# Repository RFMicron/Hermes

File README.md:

Hermes&trade;
=============

The Hermes&trade; IoT Development Platform enables exploration and development of Internet-of-Things
applications using passive wireless sensors built around the Magnus&reg;-S chip.

### Disclaimer

This material is provided "as is", without warranty of any kind, except as otherwise specified in
the individual files.

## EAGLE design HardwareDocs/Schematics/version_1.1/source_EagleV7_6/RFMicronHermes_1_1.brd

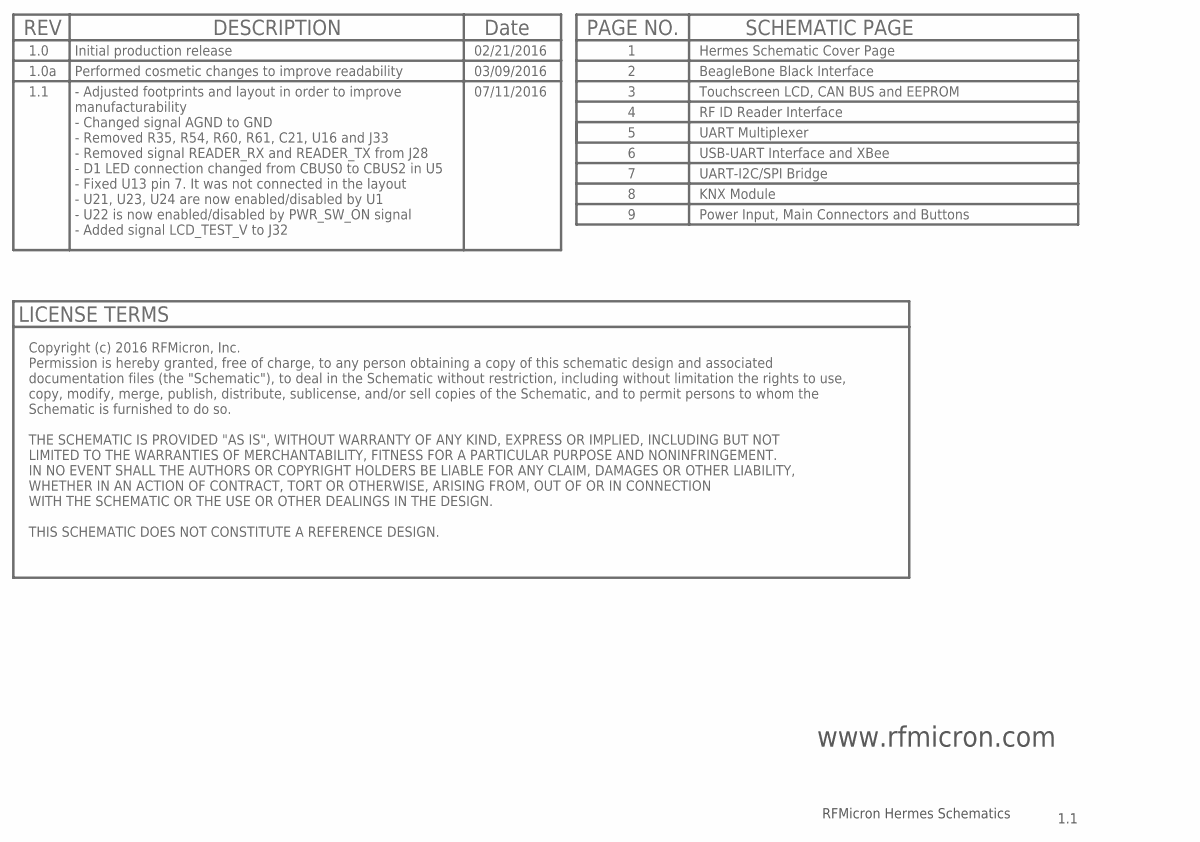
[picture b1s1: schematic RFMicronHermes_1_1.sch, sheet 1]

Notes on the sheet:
www.rfmicron.com
1.1
RFMicron Hermes Schematics
REV
DESCRIPTION
Date
02/21/2016
1.0
Initial production release
PAGE NO.
SCHEMATIC PAGE
Hermes Schematic Cover Page
LICENSE TERMS
Copyright (c) 2016 RFMicron, Inc. Permission is hereby granted, free of charge, to any person obtaining a copy of this schematic design and associated documentation files (the "Schematic"), to deal in the Schematic without restriction, including without limitation the rights to use, copy, modify, m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
BeagleBone Black Interface
Touchscreen LCD, CAN BUS and EEPROM
RF ID Reader Interface
UART Multiplexer
UART-I2C/SPI Bridge
USB-UART Interface and XBee
KNX Module
1.0a
03/09/2016
Performed cosmetic changes to improve readability
Power Input, Main Connectors and Buttons
07/11/2016
- Adjusted footprints and layout in order to improve manufacturability - Changed signal AGND to GND - Removed R35, R54, R60, R61, C21, U16 and J33 - Removed signal READER_RX and READER_TX from J28 - D1 LED connection changed from CBUS0 to CBUS2 in U5 - Fixed U13 pin 7. It was not connected in the l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

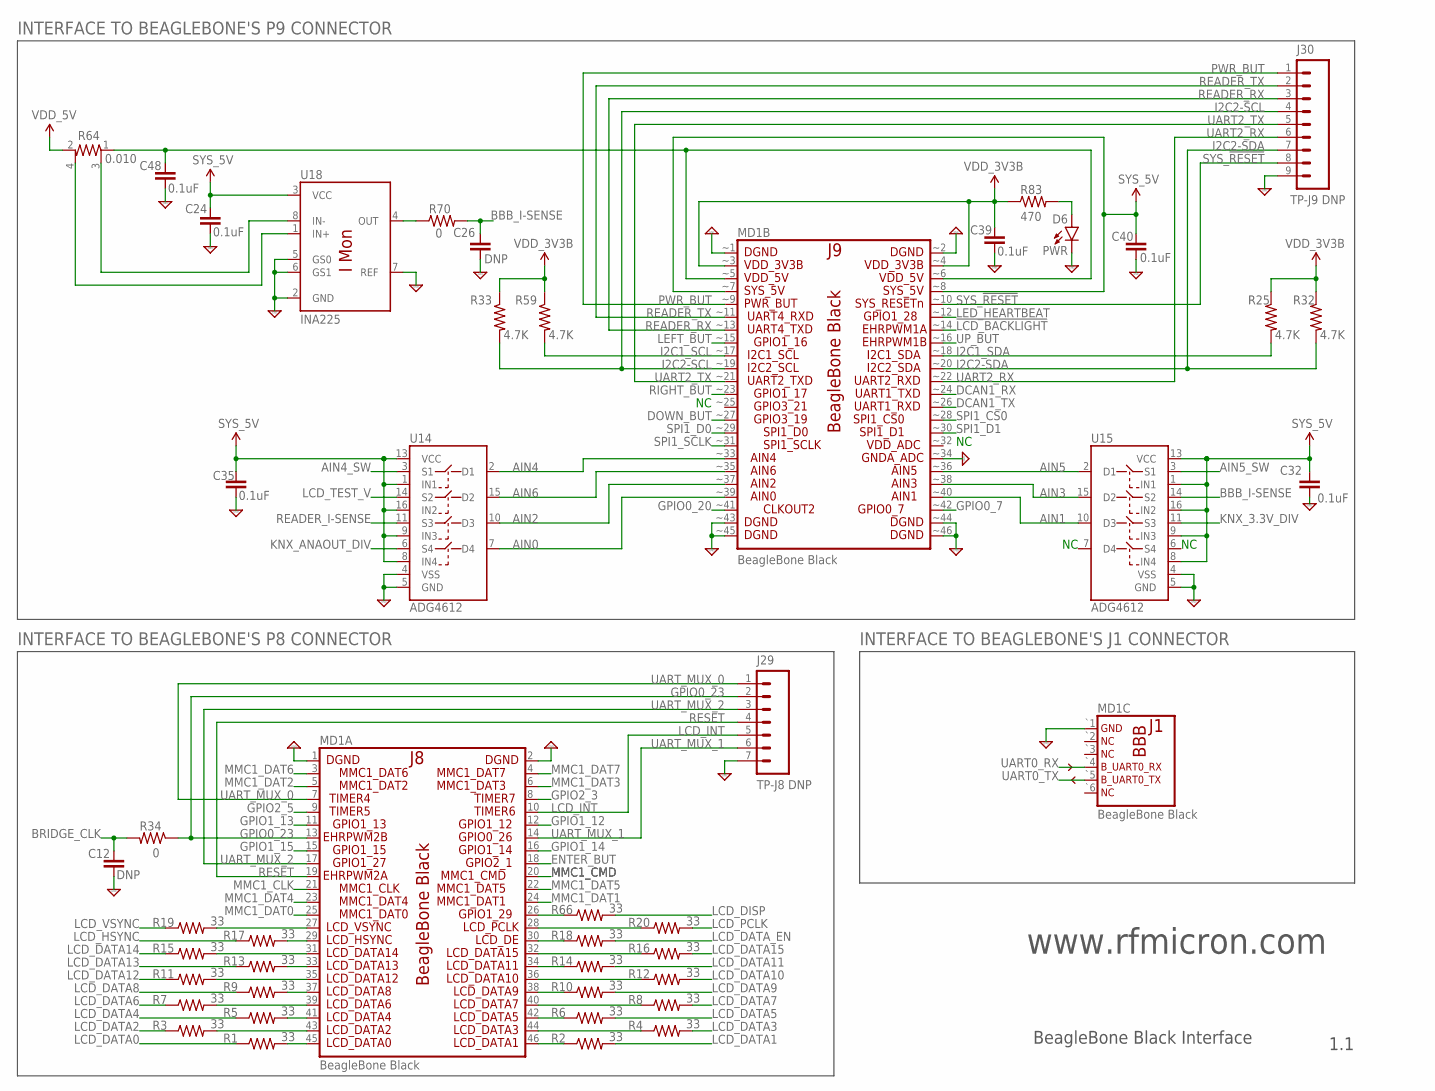
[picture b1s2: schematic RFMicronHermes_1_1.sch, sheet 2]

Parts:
C12, C26: DNP; C0603K
C24, C32, C35, C39, C40, C48: 0.1uF; C0603K
D6: PWR; LED-1206
J29: TP-J8 DNP; 1X07-SPECIAL
J30: TP-J9 DNP; 1X09-SPECIAL
MD1: BeagleBone Black; BBONE_BK
R1, R2, R3, R4, R5, R6, R7, R8, R9, R10, R11, R12, R13, R14, R15, R16, R17, R18, R19, R20, R66: 33; R0603
R25, R32, R33, R59: 4.7K; R0603
R34, R70: 0; R0603
R64: 0.010; RESIST_4-TERM_VISHAY
R83: 470; R0603
U14, U15: ADG4612; TSSOP16
U18: INA225; MSOP8

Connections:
!LCD_BACKLIGHT: MD1.~14 (14); also elsewhere on the board
AIN0: MD1.~39 (39), U14.7 (D4)
AIN1: MD1.~40 (40), U15.10 (D3)
AIN2: MD1.~37 (37), U14.10 (D3)
AIN3: MD1.~38 (38), U15.15 (D2)
AIN4: MD1.~33 (33), U14.2 (D1)
AIN4_SW: U14.3 (S1); also elsewhere on the board
AIN5: MD1.~36 (36), U15.2 (D1)
AIN5_SW: U15.3 (S1); also elsewhere on the board
AIN6: MD1.~35 (35), U14.15 (D2)
BBB_I-SENSE: C26.1 (+), R70.2, U15.14 (S2)
BBB_I-SENSE+: R64.4, U18.1 (IN+)
BBB_I-SENSE-: R64.3, U18.8 (IN-)
BRIDGE_CLK: C12.1 (+), R34.2; also elsewhere on the board
DCAN1_RX: MD1.~24 (24); also elsewhere on the board
DCAN1_TX: MD1.~26 (26); also elsewhere on the board
DOWN_BUT: MD1.~27 (27); also elsewhere on the board
ENTER_BUT: MD1.18; also elsewhere on the board
GND: C12.2 (-), C24.1 (+), C26.2 (-), C32.2 (-), C35.2 (-), C39.2 (-), C40.2 (-), C48.2 (-), D6.C, J29.7, J30.9, MD1.1, MD1.2, MD1.`1 (1), MD1.~1 (1), MD1.~2 (2), MD1.~34 (34), MD1.~43 (43), MD1.~44 (44), MD1.~45 (45), MD1.~46 (46), U14.4 (VSS), U14.5 (GND), U15.4 (VSS), U15.5 (GND), U18.2 (GND), U18.5 (GS0), U18.6 (GS1), U18.7 (REF); also elsewhere on the board
GPIO0_7: MD1.~42 (42); also elsewhere on the board
GPIO0_20: MD1.~41 (41); also elsewhere on the board
GPIO0_23: J29.2, MD1.13, R34.1
GPIO1_12: MD1.12; also elsewhere on the board
GPIO1_13: MD1.11; also elsewhere on the board
GPIO1_14: MD1.16; also elsewhere on the board
GPIO1_15: MD1.15; also elsewhere on the board
GPIO2_3: MD1.8; also elsewhere on the board
GPIO2_5: MD1.9; also elsewhere on the board
I2C1_SCL: MD1.~17 (17), R59.2; also elsewhere on the board
I2C1_SDA: MD1.~18 (18), R25.2; also elsewhere on the board
I2C2-SCL: J30.4, MD1.~19 (19), R33.2; also elsewhere on the board
I2C2-SDA: J30.7, MD1.~20 (20), R32.2; also elsewhere on the board
KNX_3.3V_DIV: U15.11 (S3); also elsewhere on the board
KNX_ANAOUT_DIV: U14.6 (S4); also elsewhere on the board
LCD_DATA0: R1.1; also elsewhere on the board
LCD_DATA1: R2.2; also elsewhere on the board
LCD_DATA2: R3.1; also elsewhere on the board
LCD_DATA3: R4.2; also elsewhere on the board
LCD_DATA4: R5.1; also elsewhere on the board
LCD_DATA5: R6.2; also elsewhere on the board
LCD_DATA6: R7.1; also elsewhere on the board
LCD_DATA7: R8.2; also elsewhere on the board
LCD_DATA8: R9.1; also elsewhere on the board
LCD_DATA9: R10.2; also elsewhere on the board
LCD_DATA10: R12.2; also elsewhere on the board
LCD_DATA11: R14.2; also elsewhere on the board
LCD_DATA12: R11.1; also elsewhere on the board
LCD_DATA13: R13.1; also elsewhere on the board
LCD_DATA14: R15.1; also elsewhere on the board
LCD_DATA15: R16.2; also elsewhere on the board
LCD_DATA_EN: R18.2; also elsewhere on the board
LCD_DISP: R66.2; also elsewhere on the board
LCD_HSYNC: R17.1; also elsewhere on the board
LCD_INT: J29.5, MD1.10; also elsewhere on the board
LCD_PCLK: R20.2; also elsewhere on the board
LCD_TEST_V: U14.14 (S2); also elsewhere on the board
LCD_VSYNC: R19.1; also elsewhere on the board
LED_HEARTBEAT: MD1.~12 (12); also elsewhere on the board
LEFT_BUT: MD1.~15 (15); also elsewhere on the board
MMC1_CLK: MD1.21
MMC1_CMD: MD1.20
MMC1_DAT0: MD1.25
MMC1_DAT1: MD1.24
MMC1_DAT2: MD1.5
MMC1_DAT3: MD1.6
MMC1_DAT4: MD1.23
MMC1_DAT5: MD1.22
MMC1_DAT6: MD1.3
MMC1_DAT7: MD1.4
unnamed: MD1.46, R2.1
unnamed: MD1.44, R4.1
unnamed: MD1.42, R6.1
unnamed: MD1.40, R8.1
unnamed: MD1.38, R10.1
unnamed: MD1.36, R12.1
unnamed: MD1.34, R14.1
unnamed: MD1.32, R16.1
unnamed: MD1.30, R18.1
unnamed: MD1.28, R20.1
unnamed: MD1.45, R1.2
unnamed: MD1.43, R3.2
unnamed: MD1.41, R5.2
unnamed: MD1.39, R7.2
unnamed: MD1.37, R9.2
unnamed: MD1.35, R11.2
unnamed: MD1.33, R13.2
unnamed: MD1.31, R15.2
unnamed: MD1.29, R17.2
unnamed: MD1.27, R19.2
unnamed: MD1.26, R66.1
unnamed: R70.1, U18.4 (OUT)
unnamed: D6.A, R83.2
PWR_BUT: J30.1, MD1.~9 (9); also elsewhere on the board
READER_I-SENSE: U14.11 (S3); also elsewhere on the board
READER_RX: J30.3, MD1.~13 (13); also elsewhere on the board
READER_TX: J30.2, MD1.~11 (11); also elsewhere on the board
RESET: J29.4, MD1.19; also elsewhere on the board
RIGHT_BUT: MD1.~23 (23); also elsewhere on the board
SPI1_CS0: MD1.~28 (28); also elsewhere on the board
SPI1_D0: MD1.~29 (29); also elsewhere on the board
SPI1_D1: MD1.~30 (30); also elsewhere on the board
SPI1_SCLK: MD1.~31 (31); also elsewhere on the board
SYS_5V: C24.2 (-), C32.1 (+), C35.1 (+), C40.1 (+), MD1.~7 (7), MD1.~8 (8), U14.1 (IN1), U14.8 (IN4), U14.9 (IN3), U14.13 (VCC), U14.16 (IN2), U15.1 (IN1), U15.8 (IN4), U15.9 (IN3), U15.13 (VCC), U15.16 (IN2), U18.3 (VCC); also elsewhere on the board
SYS_!RESET: J30.8, MD1.~10 (10); also elsewhere on the board
UART0_RX: MD1.`4 (4); also elsewhere on the board
UART0_TX: MD1.`5 (5); also elsewhere on the board
UART2_RX: J30.6, MD1.~22 (22); also elsewhere on the board
UART2_TX: J30.5, MD1.~21 (21); also elsewhere on the board
UART_MUX_0: J29.1, MD1.7; also elsewhere on the board
UART_MUX_1: J29.6, MD1.14; also elsewhere on the board
UART_MUX_2: J29.3, MD1.17; also elsewhere on the board
UP_BUT: MD1.~16 (16); also elsewhere on the board
VDD_3V3B: C39.1 (+), MD1.~3 (3), MD1.~4 (4), R25.1, R32.1, R33.1, R59.1, R83.1; also elsewhere on the board
VDD_5V: R64.2; also elsewhere on the board
VDD_5V`: C48.1 (+), MD1.~5 (5), MD1.~6 (6), R64.1

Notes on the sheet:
www.rfmicron.com
1.1
BeagleBone Black Interface
INTERFACE TO BEAGLEBONE'S J1 CONNECTOR
INTERFACE TO BEAGLEBONE'S P9 CONNECTOR
INTERFACE TO BEAGLEBONE'S P8 CONNECTOR

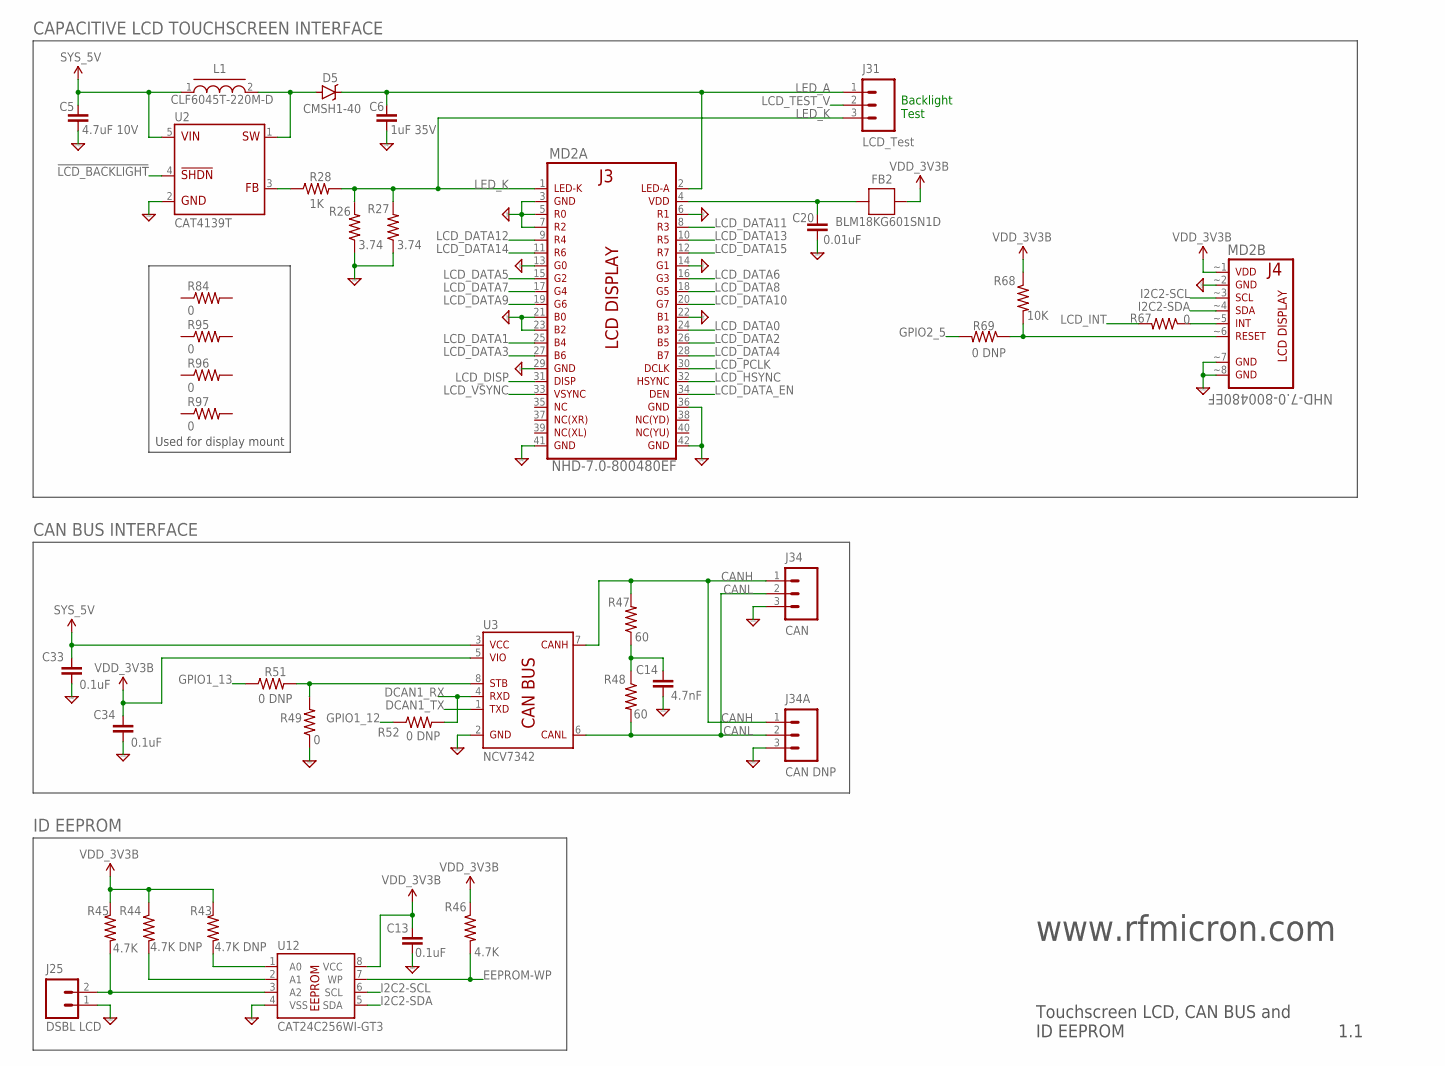
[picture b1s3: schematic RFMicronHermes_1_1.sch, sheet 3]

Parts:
C5: 4.7uF 10V; C0603K
C6: 1uF 35V; C0603K
C13, C33, C34: 0.1uF; C0603K
C14: 4.7nF; C0603K
C20: 0.01uF; C0603K
D5: CMSH1-40; SMB-DIODE
FB2: BLM18KG601SN1D; 0603
J25: DSBL LCD; 1X2SM
J31: LCD_Test; 1X03-SPECIAL
J34: CAN; PHOENIX1725669-3
J34A: CAN DNP; 1X03-SPECIAL
L1: CLF6045T-220M-D; TDK_CA
MD2: NHD-7.0-800480EF; NEWHAVEN_LCD_NHD-7.0-800480EF
R26, R27: 3.74; R0603
R28: 1K; R0603
R43, R44: 4.7K DNP; R0603
R45, R46: 4.7K; R0603
R47, R48: 60; R0603
R49, R67: 0; R0603
R51, R52, R69: 0 DNP; R0603
R68: 10K; R0603
R84, R95, R96, R97: 0; 0805-RES
U2: CAT4139T; TSOT-23-5
U3: NCV7342; SOIC08
U12: CAT24C256WI-GT3; SO08

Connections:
!LCD_BACKLIGHT: U2.4 (!SHDN); also elsewhere on the board
CANH: J34.1, J34A.1, R47.2, U3.7 (CANH)
CANL: J34.2, J34A.2, R48.2, U3.6 (CANL)
DCAN1_RX: R52.2, U3.4 (RXD); also elsewhere on the board
DCAN1_TX: U3.1 (TXD); also elsewhere on the board
EEPROM-WP: R46.2, U12.7 (WP); also elsewhere on the board
GND: C5.2 (-), C6.2 (-), C13.2 (-), C14.2 (-), C20.2 (-), C33.2 (-), C34.2 (-), J25.1, J34.3, J34A.3, MD2.3, MD2.5, MD2.6, MD2.7, MD2.13, MD2.14, MD2.21, MD2.22, MD2.23, MD2.29, MD2.36, MD2.41, MD2.42, MD2.~2 (2), MD2.~7 (7), MD2.~8 (8), R26.1, R27.1, R49.1, U2.2 (GND), U3.2 (GND), U12.4 (VSS); also elsewhere on the board
GPIO1_12: R52.1; also elsewhere on the board
GPIO1_13: R51.1; also elsewhere on the board
GPIO2_5: R69.2; also elsewhere on the board
I2C2-SCL: MD2.~3 (3), U12.6 (SCL); also elsewhere on the board
I2C2-SDA: MD2.~4 (4), U12.5 (SDA); also elsewhere on the board
LCD_DATA0: MD2.24; also elsewhere on the board
LCD_DATA1: MD2.25; also elsewhere on the board
LCD_DATA2: MD2.26; also elsewhere on the board
LCD_DATA3: MD2.27; also elsewhere on the board
LCD_DATA4: MD2.28; also elsewhere on the board
LCD_DATA5: MD2.15; also elsewhere on the board
LCD_DATA6: MD2.16; also elsewhere on the board
LCD_DATA7: MD2.17; also elsewhere on the board
LCD_DATA8: MD2.18; also elsewhere on the board
LCD_DATA9: MD2.19; also elsewhere on the board
LCD_DATA10: MD2.20; also elsewhere on the board
LCD_DATA11: MD2.8; also elsewhere on the board
LCD_DATA12: MD2.9; also elsewhere on the board
LCD_DATA13: MD2.10; also elsewhere on the board
LCD_DATA14: MD2.11; also elsewhere on the board
LCD_DATA15: MD2.12; also elsewhere on the board
LCD_DATA_EN: MD2.34; also elsewhere on the board
LCD_DISP: MD2.31; also elsewhere on the board
LCD_HSYNC: MD2.32; also elsewhere on the board
LCD_INT: R67.2; also elsewhere on the board
LCD_PCLK: MD2.30; also elsewhere on the board
LCD_TEST_V: J31.2; also elsewhere on the board
LCD_VSYNC: MD2.33; also elsewhere on the board
LED_A: C6.1 (+), D5.C, J31.1, MD2.2
LED_K: J31.3, MD2.1, R26.2, R27.2, R28.2
unnamed: R43.2, U12.1 (A0)
unnamed: D5.A, L1.2, U2.1 (SW)
unnamed: R44.2, U12.2 (A1)
unnamed: J25.2, R45.2, U12.3 (A2)
unnamed: R28.1, U2.3 (FB)
unnamed: C14.1 (+), R47.1, R48.1
unnamed: R49.2, R51.2, U3.8 (STB)
unnamed: C20.1 (+), FB2.2, MD2.4
unnamed: MD2.~6 (6), R68.2, R69.1
unnamed: MD2.~5 (5), R67.1
SYS_5V: C5.1 (+), C33.1 (+), L1.1, U2.5 (VIN), U3.3 (VCC); also elsewhere on the board
VDD_3V3B: C13.1 (+), C34.1 (+), FB2.1, MD2.~1 (1), R43.1, R44.1, R45.1, R46.1, R68.1, U3.5 (VIO), U12.8 (VCC); also elsewhere on the board

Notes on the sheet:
Backlight Test
Used for display mount
www.rfmicron.com
1.1
Touchscreen LCD, CAN BUS and ID EEPROM
CAPACITIVE LCD TOUCHSCREEN INTERFACE
CAN BUS INTERFACE
ID EEPROM

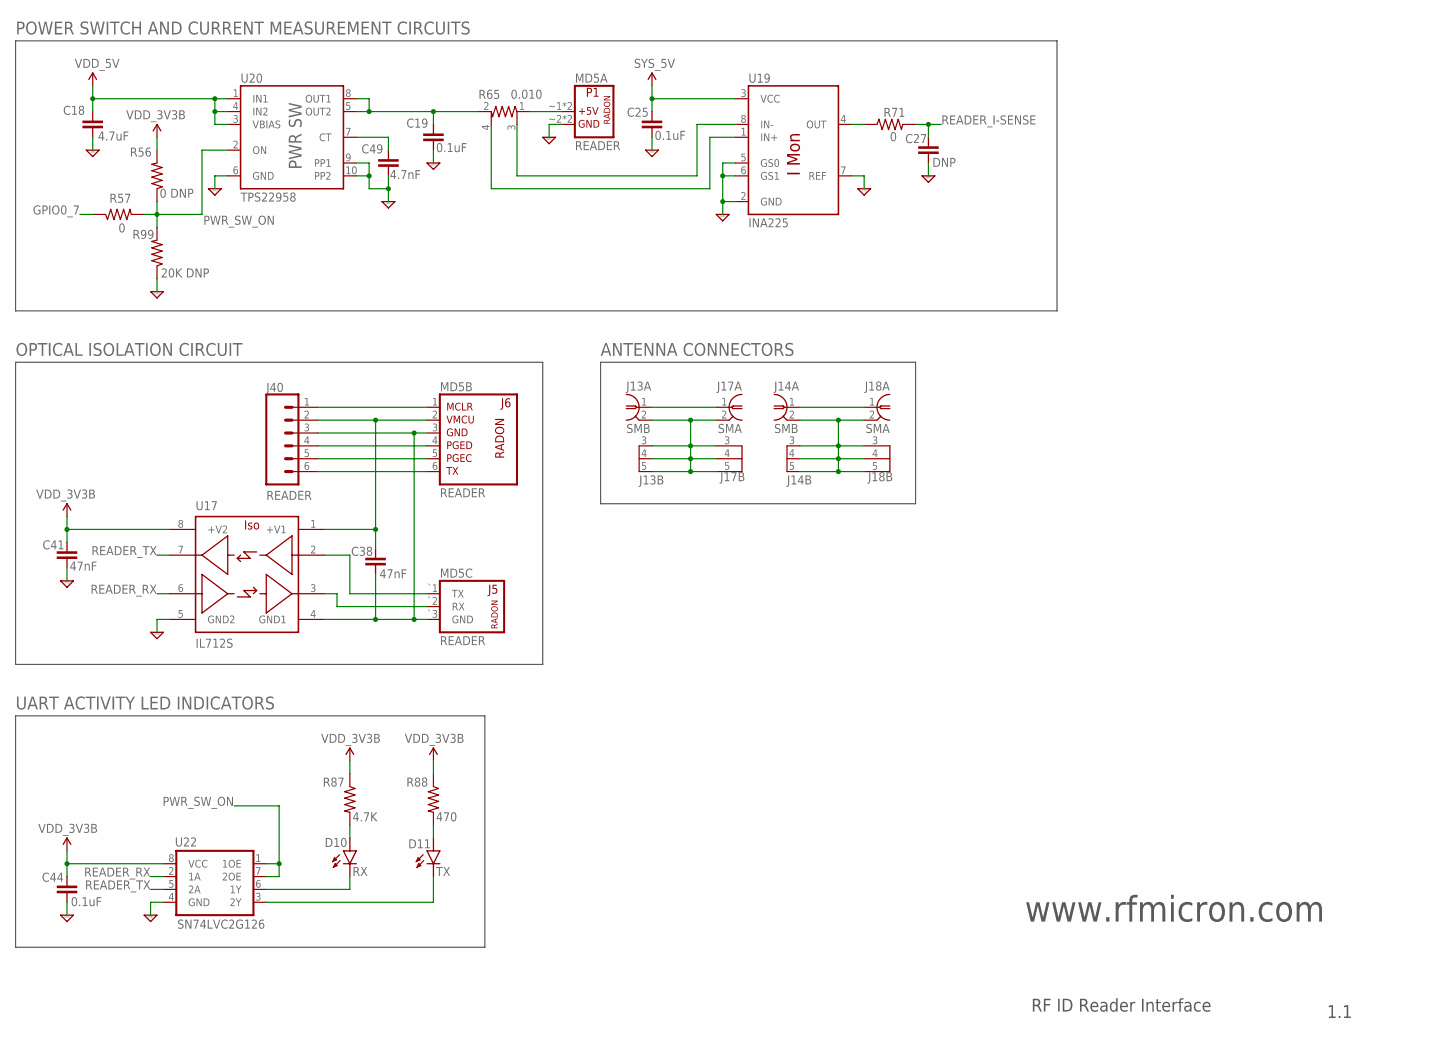
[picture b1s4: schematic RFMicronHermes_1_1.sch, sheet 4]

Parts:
C18: 4.7uF; C0603K
C19, C25, C44: 0.1uF; C0603K
C27: DNP; C0603K
C38, C41: 47nF; C0603K
C49: 4.7nF; C0603K
D10: RX; LED-1206
D11: TX; LED-1206
J13, J14: SMB; SMB-SMD
J17, J18: SMA; SMA-EDGE
J40: READER; 1X06
MD5: READER; RADON_RFID_READ
R56: 0 DNP; R0603
R57, R71: 0; R0603
R65: 0.010; RESIST_4-TERM_VISHAY
R87: 4.7K; R0603
R88: 470; R0603
R99: 20K DNP; R0603
U17: IL712S; SOIC08
U19: INA225; MSOP8
U20: TPS22958; MSOP8-POWERPAD
U22: SN74LVC2G126; SM8-TI-A

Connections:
GND: C18.2 (-), C19.2 (-), C25.1 (+), C27.2 (-), C41.2 (-), C44.1 (+), C49.2 (-), MD5.~2 (2), MD5.~4 (2), R99.1, U17.5 (GND2), U19.2 (GND), U19.5 (GS0), U19.6 (GS1), U19.7 (REF), U20.6 (GND), U20.9 (PP1), U20.10 (PP2), U22.4 (GND); also elsewhere on the board
GND_RF: J13.2 (GND), J13.3 (GND), J13.4 (GND), J13.5 (GND), J17.2 (GND), J17.3 (GND), J17.4 (GND), J17.5 (GND)
GPIO0_7: R57.1; also elsewhere on the board
unnamed: J13.1, J17.1
unnamed: J14.1, J18.1
unnamed: J40.1, MD5.1
unnamed: J14.2 (GND), J14.3 (GND), J14.4 (GND), J14.5 (GND), J18.2 (GND), J18.3 (GND), J18.4 (GND), J18.5 (GND)
unnamed: J40.4, MD5.4
unnamed: J40.5, MD5.5
unnamed: C49.1 (+), U20.7 (CT)
unnamed: J40.6, MD5.6
unnamed: C38.2 (-), J40.3, MD5.3, MD5.`3 (GND), U17.4 (GND1)
unnamed: MD5.`2 (RX), U17.3 (OUT2)
unnamed: MD5.`1 (TX), U17.2 (IN1)
unnamed: D10.A, R87.2
unnamed: D11.A, R88.2
unnamed: D10.C, U22.6 (1Y)
unnamed: C38.1 (+), J40.2, MD5.2 (VMCU), U17.1 (+V1)
unnamed: D11.C, U22.3 (2Y)
unnamed: R71.1, U19.4 (OUT)
PWR_SW_ON: R56.1, R57.2, R99.2, U20.2 (ON), U22.1 (1OE), U22.7 (2OE)
READER_I-SENSE: C27.1 (+), R71.2; also elsewhere on the board
READER_I-SENSE+: R65.4, U19.1 (IN+)
READER_I-SENSE-: R65.3, U19.8 (IN-)
READER_RX: U17.6 (IN2), U22.2 (1A); also elsewhere on the board
READER_TX: U17.7 (OUT1), U22.5 (2A); also elsewhere on the board
SYS_5V: C25.2 (-), U19.3 (VCC); also elsewhere on the board
VDD_3V3B: C41.1 (+), C44.2 (-), R56.2, R87.1, R88.1, U17.8 (+V2), U22.8 (VCC); also elsewhere on the board
VDD_5V: C18.1 (+), U20.1 (IN1), U20.3 (VBIAS), U20.4 (IN2); also elsewhere on the board
VDD_5V-SW: MD5.~1 (1), MD5.~3 (1), R65.1
VDD_5V-SW`: C19.1 (+), R65.2, U20.5 (OUT2), U20.8 (OUT1)

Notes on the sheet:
www.rfmicron.com
1.1
RF ID Reader Interface
POWER SWITCH AND CURRENT MEASUREMENT CIRCUITS
OPTICAL ISOLATION CIRCUIT
ANTENNA CONNECTORS
UART ACTIVITY LED INDICATORS

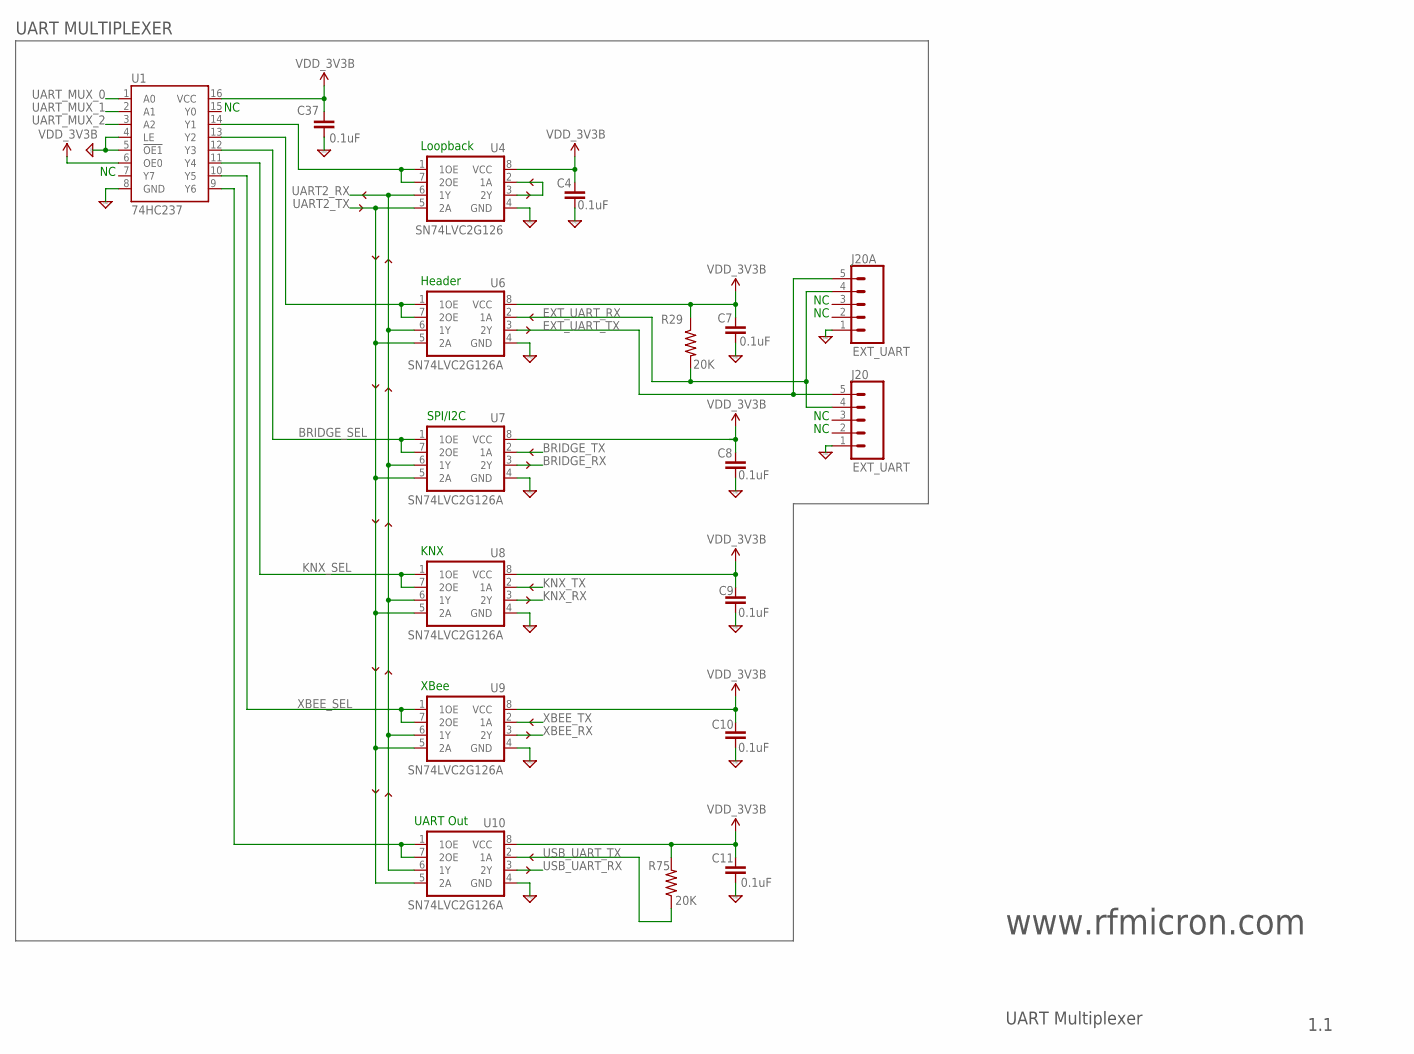
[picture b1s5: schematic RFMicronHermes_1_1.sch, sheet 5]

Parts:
C4, C7, C8, C9, C10, C11, C37: 0.1uF; C0603K
J20: EXT_UART; PHOENIX1725685-5
J20A: EXT_UART; 1X05
R29, R75: 20K; R0603
U1: 74HC237; TSSOP16
U4: SN74LVC2G126; SM8-TI-A
U6, U7, U8, U9, U10: SN74LVC2G126A; SM8-TI-A

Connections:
BRIDGE_RX: U7.3 (2Y); also elsewhere on the board
BRIDGE_SEL: U1.12 (Y3), U7.1 (1OE), U7.7 (2OE); also elsewhere on the board
BRIDGE_TX: U7.2 (1A); also elsewhere on the board
EXT_UART_RX: J20.4, J20A.4, R29.2, U6.2 (1A); also elsewhere on the board
EXT_UART_TX: J20.5, J20A.5, U6.3 (2Y); also elsewhere on the board
GND: C4.1 (+), C7.1 (+), C8.1 (+), C9.1 (+), C10.1 (+), C11.1 (+), C37.2 (-), J20.1, J20A.1, U1.4 (LE), U1.5 (!OE1), U1.8 (GND), U4.4 (GND), U6.4 (GND), U7.4 (GND), U8.4 (GND), U9.4 (GND), U10.4 (GND); also elsewhere on the board
KNX_RX: U8.3 (2Y); also elsewhere on the board
KNX_SEL: U1.11 (Y4), U8.1 (1OE), U8.7 (2OE); also elsewhere on the board
KNX_TX: U8.2 (1A); also elsewhere on the board
unnamed: U4.2 (1A), U4.3 (2Y)
unnamed: U1.14 (Y1), U4.1 (1OE), U4.7 (2OE)
unnamed: U1.13 (Y2), U6.1 (1OE), U6.7 (2OE)
unnamed: U1.9 (Y6), U10.1 (1OE), U10.7 (2OE)
UART2_RX: U4.6 (1Y), U6.6 (1Y), U7.6 (1Y), U8.6 (1Y), U9.6 (1Y), U10.6 (1Y); also elsewhere on the board
UART2_TX: U4.5 (2A), U6.5 (2A), U7.5 (2A), U8.5 (2A), U9.5 (2A), U10.5 (2A); also elsewhere on the board
UART_MUX_0: U1.1 (A0); also elsewhere on the board
UART_MUX_1: U1.2 (A1); also elsewhere on the board
UART_MUX_2: U1.3 (A2); also elsewhere on the board
USB_UART_RX: U10.3 (2Y); also elsewhere on the board
USB_UART_TX: R75.1, U10.2 (1A); also elsewhere on the board
VDD_3V3B: C4.2 (-), C7.2 (-), C8.2 (-), C9.2 (-), C10.2 (-), C11.2 (-), C37.1 (+), R29.1, R75.2, U1.6 (OE0), U1.16 (VCC), U4.8 (VCC), U6.8 (VCC), U7.8 (VCC), U8.8 (VCC), U9.8 (VCC), U10.8 (VCC); also elsewhere on the board
XBEE_RX: U9.3 (2Y); also elsewhere on the board
XBEE_SEL: U1.10 (Y5), U9.1 (1OE), U9.7 (2OE); also elsewhere on the board
XBEE_TX: U9.2 (1A); also elsewhere on the board

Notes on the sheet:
KNX
SPI/I2C
Header
Loopback
XBee
UART Out
www.rfmicron.com
1.1
UART Multiplexer
UART MULTIPLEXER

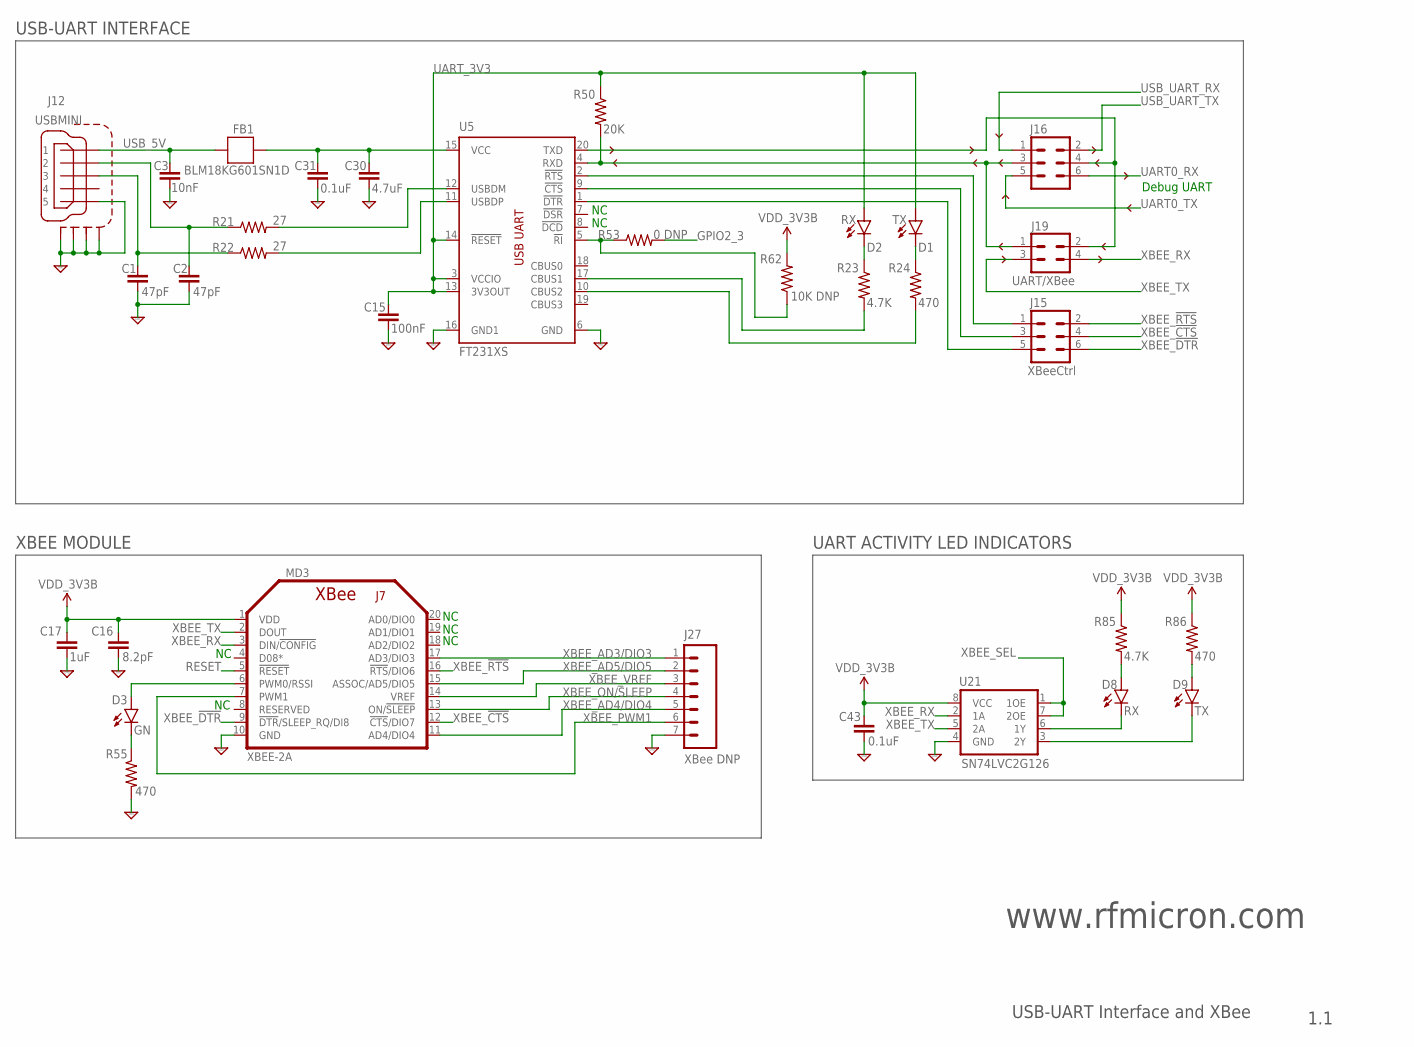
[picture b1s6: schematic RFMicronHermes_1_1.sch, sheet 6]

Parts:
C1, C2: 47pF; C0603K
C3: 10nF; C0603K
C15: 100nF; C0603K
C16: 8.2pF; C0603K
C17: 1uF; C0603K
C30: 4.7uF; C0603K
C31, C43: 0.1uF; C0603K
D1, D9: TX; LED-1206
D2, D8: RX; LED-1206
D3: GN; LED-1206
FB1: BLM18KG601SN1D; 0603
J12: USBMINI; USBMINI-TH
J15: XBeeCtrl; 2X3
J16: M03X2SM; 2X3SM
J19: UART/XBee; 2X2SM
J27: XBee DNP; 1X07-SPECIAL
MD3: XBEE-2A; XBEE-2
R21, R22: 27; R0603
R23, R85: 4.7K; R0603
R24, R55, R86: 470; R0603
R50: 20K; R0603
R53: 0 DNP; R0603
R62: 10K DNP; R0603
U5: FT231XS; SSOP20-.150
U21: SN74LVC2G126; SM8-TI-A

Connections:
!CTS: J15.3, U5.9 (!CTS)
!DTR: J15.5, U5.1 (!DTR)
!RTS: J15.1, U5.2 (!RTS)
GND: C1.2 (-), C2.2 (-), C3.2 (-), C15.2 (-), C16.2 (-), C17.2 (-), C30.2 (-), C31.2 (-), C43.1 (+), J12.5, J12.6 (S1), J12.7 (S2), J12.8 (S3), J12.9 (S4), J27.7, MD3.10 (GND), R55.2, U5.6 (GND), U5.16 (GND1), U21.4 (GND); also elsewhere on the board
GPIO2_3: R53.2; also elsewhere on the board
unnamed: R21.2, U5.12 (USBDM)
unnamed: R22.2, U5.11 (USBDP)
unnamed: C2.1 (+), J12.2, R21.1
unnamed: C1.1 (+), J12.3, R22.1
unnamed: C30.1 (+), C31.1 (+), FB1.1, U5.15 (VCC)
unnamed: D3.C, R55.1
unnamed: D1.C, R24.1
unnamed: D2.C, R23.1
unnamed: D3.A, MD3.6 (PWM0/RSSI)
unnamed: R23.2, U5.17 (CBUS1)
unnamed: R53.1, R62.1, U5.5 (!RI)
unnamed: R24.2, U5.10 (CBUS2)
unnamed: D8.A, R85.2
unnamed: J16.3, J19.1, R50.2, U5.4 (RXD)
unnamed: D9.A, R86.2
unnamed: D8.C, U21.6 (1Y)
unnamed: D9.C, U21.3 (2Y)
unnamed: J16.4, J19.2, U5.20 (TXD)
RESET: MD3.5 (!RESET); also elsewhere on the board
UART0_RX: J16.6; also elsewhere on the board
UART0_TX: J16.5; also elsewhere on the board
UART_3V3: C15.1 (+), D1.A, D2.A, R50.1, U5.3 (VCCIO), U5.13 (3V3OUT), U5.14 (!RESET)
USB_5V: C3.1 (+), FB1.2, J12.1
USB_UART_RX: J16.1; also elsewhere on the board
USB_UART_TX: J16.2; also elsewhere on the board
VDD_3V3B: C16.1 (+), C17.1 (+), C43.2 (-), MD3.1 (VDD), R62.2, R85.1, R86.1, U21.8 (VCC); also elsewhere on the board
XBEE_!CTS: J15.4, MD3.12 (!CTS!/DIO7)
XBEE_!DTR: J15.6, MD3.9 (!DTR!/SLEEP_RQ/DI8)
XBEE_!RTS: J15.2, MD3.16 (!RTS!/DIO6)
XBEE_AD3/DIO3: J27.1, MD3.17 (AD3/DIO3)
XBEE_AD4/DIO4: J27.5, MD3.11 (AD4/DIO4)
XBEE_AD5/DIO5: J27.2, MD3.15 (ASSOC/AD5/DIO5)
XBEE_ON/SLEEP: J27.4, MD3.13 (ON/!SLEEP)
XBEE_PWM1: J27.6, MD3.7 (PWM1)
XBEE_RX: J19.4, MD3.3 (DIN/!CONFIG), U21.2 (1A); also elsewhere on the board
XBEE_SEL: U21.1 (1OE), U21.7 (2OE); also elsewhere on the board
XBEE_TX: J19.3, MD3.2 (DOUT), U21.5 (2A); also elsewhere on the board
XBEE_VREF: J27.3, MD3.14 (VREF)

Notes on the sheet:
www.rfmicron.com
1.1
USB-UART Interface and XBee
Debug UART
UART ACTIVITY LED INDICATORS
XBEE MODULE
USB-UART INTERFACE

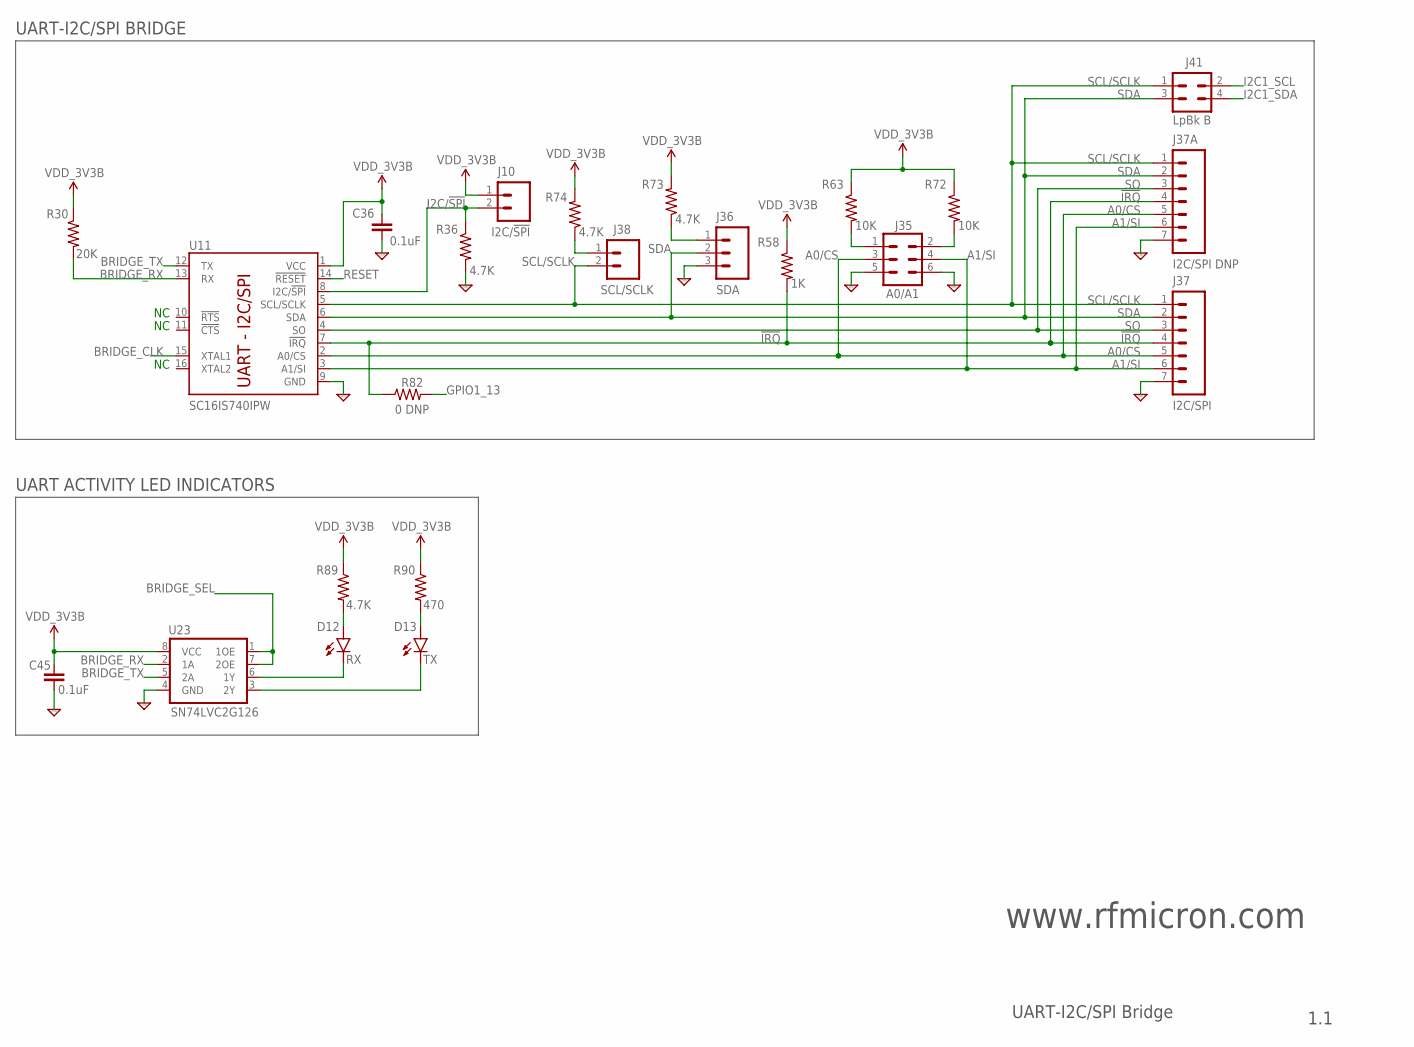
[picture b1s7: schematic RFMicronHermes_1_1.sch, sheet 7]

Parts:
C36, C45: 0.1uF; C0603K
D12: RX; LED-1206
D13: TX; LED-1206
J10: I2C/!SPI; 1X2
J35: A0/A1; 2X3SM
J36: SDA; 1X03-SPECIAL
J37: I2C/SPI; PHOENIX1725708-7
J37A: I2C/SPI DNP; 1X07-SPECIAL
J38: SCL/SCLK; 1X2
J41: LpBk B; 2X2SM
R30: 20K; R0603
R36, R73, R74, R89: 4.7K; R0603
R58: 1K; R0603
R63, R72: 10K; R0603
R82: 0 DNP; R0603
R90: 470; R0603
U11: SC16IS740IPW; TSSOP16
U23: SN74LVC2G126; SM8-TI-A

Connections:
!IRQ: J37.4, J37A.4, R58.2, R82.1, U11.7 (!IRQ)
A0/CS: J35.3, J37.5, J37A.5, U11.2 (A0/CS); also elsewhere on the board
A1/SI: J35.4, J37.6, J37A.6, U11.3 (A1/SI); also elsewhere on the board
BRIDGE_CLK: U11.15 (XTAL1); also elsewhere on the board
BRIDGE_RX: R30.2, U11.13 (RX), U23.2 (1A); also elsewhere on the board
BRIDGE_SEL: U23.1 (1OE), U23.7 (2OE); also elsewhere on the board
BRIDGE_TX: U11.12 (TX), U23.5 (2A); also elsewhere on the board
GND: C36.2 (-), C45.1 (+), J35.5, J35.6, J36.3, J37.7, J37A.7, R36.2, U11.9 (GND), U23.4 (GND); also elsewhere on the board
GPIO1_13: R82.2; also elsewhere on the board
I2C1_SCL: J41.2; also elsewhere on the board
I2C1_SDA: J41.4; also elsewhere on the board
I2C/!SPI: J10.2, R36.1, U11.8 (I2C/!SPI)
unnamed: J38.1, R74.1
unnamed: J36.1, R73.1
unnamed: J35.1, R63.2
unnamed: J35.2, R72.2
unnamed: D12.A, R89.2
unnamed: D13.A, R90.2
unnamed: D12.C, U23.6 (1Y)
unnamed: D13.C, U23.3 (2Y)
RESET: U11.14 (!RESET); also elsewhere on the board
SCL/SCLK: J37.1, J37A.1, J38.2, J41.1, U11.5 (SCL/SCLK); also elsewhere on the board
SDA: J36.2, J37.2, J37A.2, J41.3, U11.6 (SDA)
SO: J37.3, J37A.3, U11.4 (SO); also elsewhere on the board
VDD_3V3B: C36.1 (+), C45.2 (-), J10.1, R30.1, R58.1, R63.1, R72.1, R73.2, R74.2, R89.1, R90.1, U11.1 (VCC), U23.8 (VCC); also elsewhere on the board

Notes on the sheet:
www.rfmicron.com
1.1
UART-I2C/SPI Bridge
UART ACTIVITY LED INDICATORS
UART-I2C/SPI BRIDGE
